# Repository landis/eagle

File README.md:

eagle
=====

eagle schematics and boards

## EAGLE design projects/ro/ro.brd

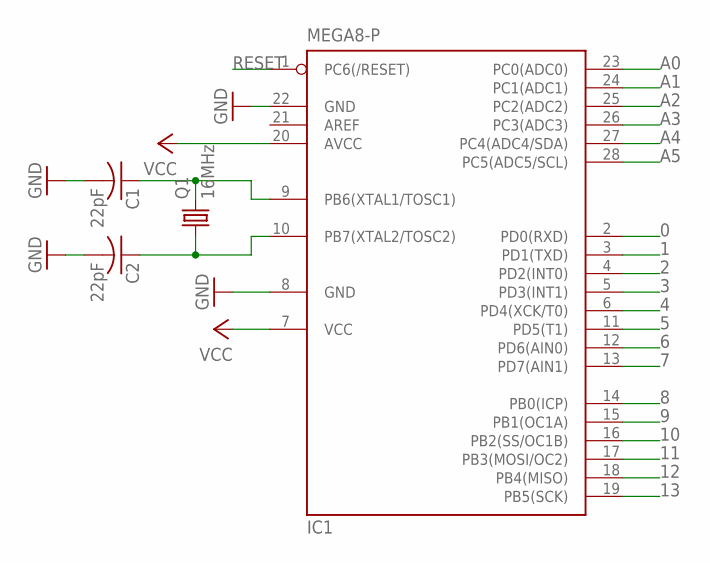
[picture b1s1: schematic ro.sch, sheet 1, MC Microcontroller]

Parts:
C1, C2: 22pF; C025-025X050
IC1: MEGA8-P; DIL28-3
Q1: 16MHz; HC49/S

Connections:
0: IC1.2 (PD0(RXD))
1: IC1.3 (PD1(TXD))
2: IC1.4 (PD2(INT0)); also elsewhere on the board
3: IC1.5 (PD3(INT1)); also elsewhere on the board
4: IC1.6 (PD4(XCK/T0))
5: IC1.11 (PD5(T1))
6: IC1.12 (PD6(AIN0))
7: IC1.13 (PD7(AIN1)); also elsewhere on the board
8: IC1.14 (PB0(ICP)); also elsewhere on the board
9: IC1.15 (PB1(OC1A)); also elsewhere on the board
10: IC1.16 (PB2(SS/OC1B)); also elsewhere on the board
11: IC1.17 (PB3(MOSI/OC2)); also elsewhere on the board
12: IC1.18 (PB4(MISO)); also elsewhere on the board
13: IC1.19 (PB5(SCK))
A0: IC1.23 (PC0(ADC0))
A1: IC1.24 (PC1(ADC1))
A2: IC1.25 (PC2(ADC2))
A3: IC1.26 (PC3(ADC3)); also elsewhere on the board
A4: IC1.27 (PC4(ADC4/SDA)); also elsewhere on the board
A5: IC1.28 (PC5(ADC5/SCL)); also elsewhere on the board
GND: C1.2, C2.2, IC1.8 (GND), IC1.22 (GND); also elsewhere on the board
unnamed: C1.1, IC1.9 (PB6(XTAL1/TOSC1)), Q1.2
unnamed: C2.1, IC1.10 (PB7(XTAL2/TOSC2)), Q1.1
RESET: IC1.1 (PC6(/RESET)); also elsewhere on the board
VCC: IC1.7 (VCC), IC1.20 (AVCC); also elsewhere on the board

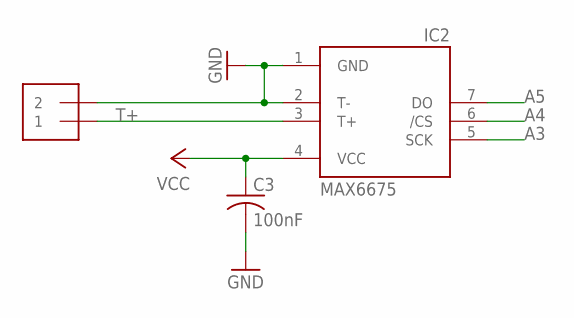
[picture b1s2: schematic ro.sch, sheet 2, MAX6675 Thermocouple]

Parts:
C3: 100nF; C025-025X050
IC2: MAX6675; SO08
TC: 1X2-3.5MM

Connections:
A3: IC2.5 (SCK); also elsewhere on the board
A4: IC2.6 (/CS); also elsewhere on the board
A5: IC2.7 (DO); also elsewhere on the board
GND: C3.2, IC2.1 (GND), IC2.2 (T-), TC.2; also elsewhere on the board
T+: IC2.3 (T+), TC.1
VCC: C3.1, IC2.4 (VCC); also elsewhere on the board

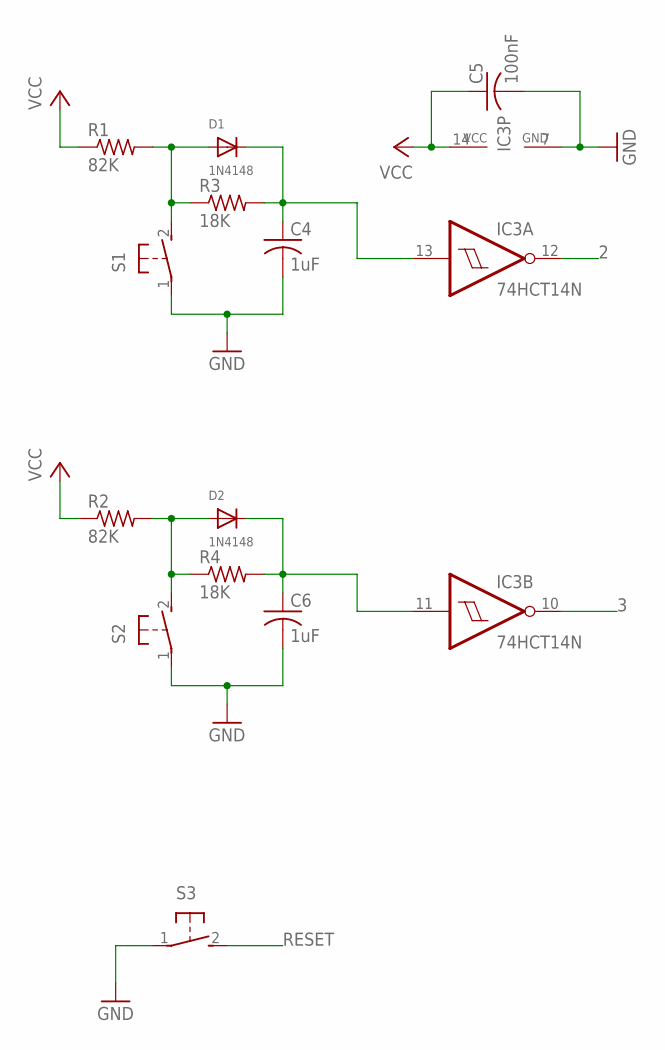
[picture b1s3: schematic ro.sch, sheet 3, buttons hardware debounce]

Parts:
C4, C6: 1uF; C0805
C5: 100nF; C0805
D1, D2: 1N4148; SMADIODE
IC3: 74HCT14N; DIL14
R1, R2: 82K; R0805
R3, R4: 18K; R0805
S1, S2, S3: 31-XX; B3F-31XX

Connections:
2: IC3.12 (O); also elsewhere on the board
3: IC3.10 (O); also elsewhere on the board
GND: C4.2, C5.2, C6.2, IC3.7 (GND), S1.1, S2.1, S3.1; also elsewhere on the board
unnamed: D1.A, R1.2, R3.1, S1.2 (S)
unnamed: D2.A, R2.2, R4.1, S2.2 (S)
unnamed: C4.1, D1.C, IC3.13 (I), R3.2
unnamed: C6.1, D2.C, IC3.11 (I), R4.2
RESET: S3.2 (S); also elsewhere on the board
VCC: C5.1, IC3.14 (VCC), R1.1, R2.1; also elsewhere on the board

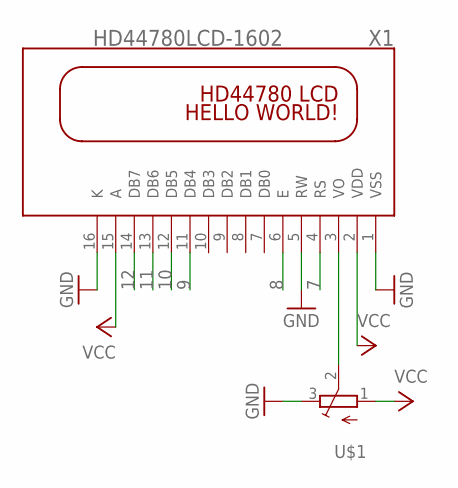
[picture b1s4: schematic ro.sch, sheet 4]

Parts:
U$1: TRIMPOTTC33X; TC33X
X1: HD44780LCD-1602; LCD1602

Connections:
7: X1.4 (RS); also elsewhere on the board
8: X1.6 (E); also elsewhere on the board
9: X1.11 (DB4); also elsewhere on the board
10: X1.12 (DB5); also elsewhere on the board
11: X1.13 (DB6); also elsewhere on the board
12: X1.14 (DB7); also elsewhere on the board
GND: U$1.3 (E), X1.1 (VSS), X1.5 (RW), X1.16 (K); also elsewhere on the board
unnamed: U$1.2 (S), X1.3 (VO)
VCC: U$1.1 (A), X1.2 (VDD), X1.15 (A); also elsewhere on the board

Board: 2 copper layers, 22 parts (1 on the bottom side), 22 nets, no tracks yet.

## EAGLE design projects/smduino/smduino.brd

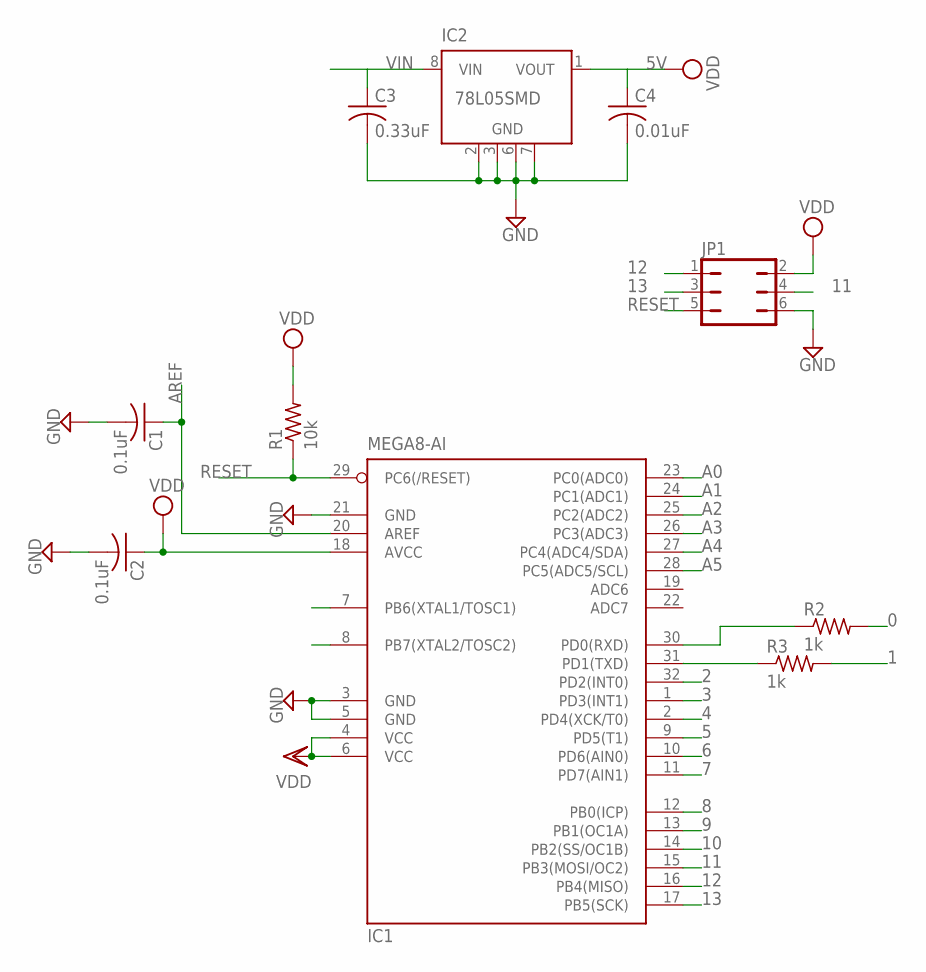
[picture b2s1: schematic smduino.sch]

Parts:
C1, C2: 0.1uF; C0603
C3: 0.33uF; C0603
C4: 0.01uF; C0603
IC1: MEGA8-AI; TQFP32-08
IC2: 78L05SMD; SO08
JP1: JP3Q
R1: 10k; R0603
R2, R3: 1k; R0603

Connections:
0: R2.2
1: R3.2
2: IC1.32 (PD2(INT0))
3: IC1.1 (PD3(INT1))
4: IC1.2 (PD4(XCK/T0))
5: IC1.9 (PD5(T1))
5V: C2.1, C4.1, IC1.4 (VCC), IC1.6 (VCC), IC1.18 (AVCC), IC2.1 (VOUT), JP1.2, R1.2
6: IC1.10 (PD6(AIN0))
7: IC1.11 (PD7(AIN1))
8: IC1.12 (PB0(ICP))
9: IC1.13 (PB1(OC1A))
10: IC1.14 (PB2(SS/OC1B))
11: IC1.15 (PB3(MOSI/OC2)), JP1.4
12: IC1.16 (PB4(MISO)), JP1.1
13: IC1.17 (PB5(SCK)), JP1.3
A0: IC1.23 (PC0(ADC0))
A1: IC1.24 (PC1(ADC1))
A2: IC1.25 (PC2(ADC2))
A3: IC1.26 (PC3(ADC3))
A4: IC1.27 (PC4(ADC4/SDA))
A5: IC1.28 (PC5(ADC5/SCL))
AREF: C1.1, IC1.20 (AREF)
GND: C1.2, C2.2, C3.2, C4.2, IC1.3 (GND), IC1.5 (GND), IC1.21 (GND), IC2.2 (GND), IC2.3 (GND), IC2.6 (GND), IC2.7 (GND), JP1.6
unnamed: IC1.30 (PD0(RXD)), R2.1
unnamed: IC1.31 (PD1(TXD)), R3.1
RESET: IC1.29 (PC6(/RESET)), JP1.5, R1.1
VIN: C3.1, IC2.8 (VIN)
XTAL1: IC1.7 (PB6(XTAL1/TOSC1))
XTAL2: IC1.8 (PB7(XTAL2/TOSC2))

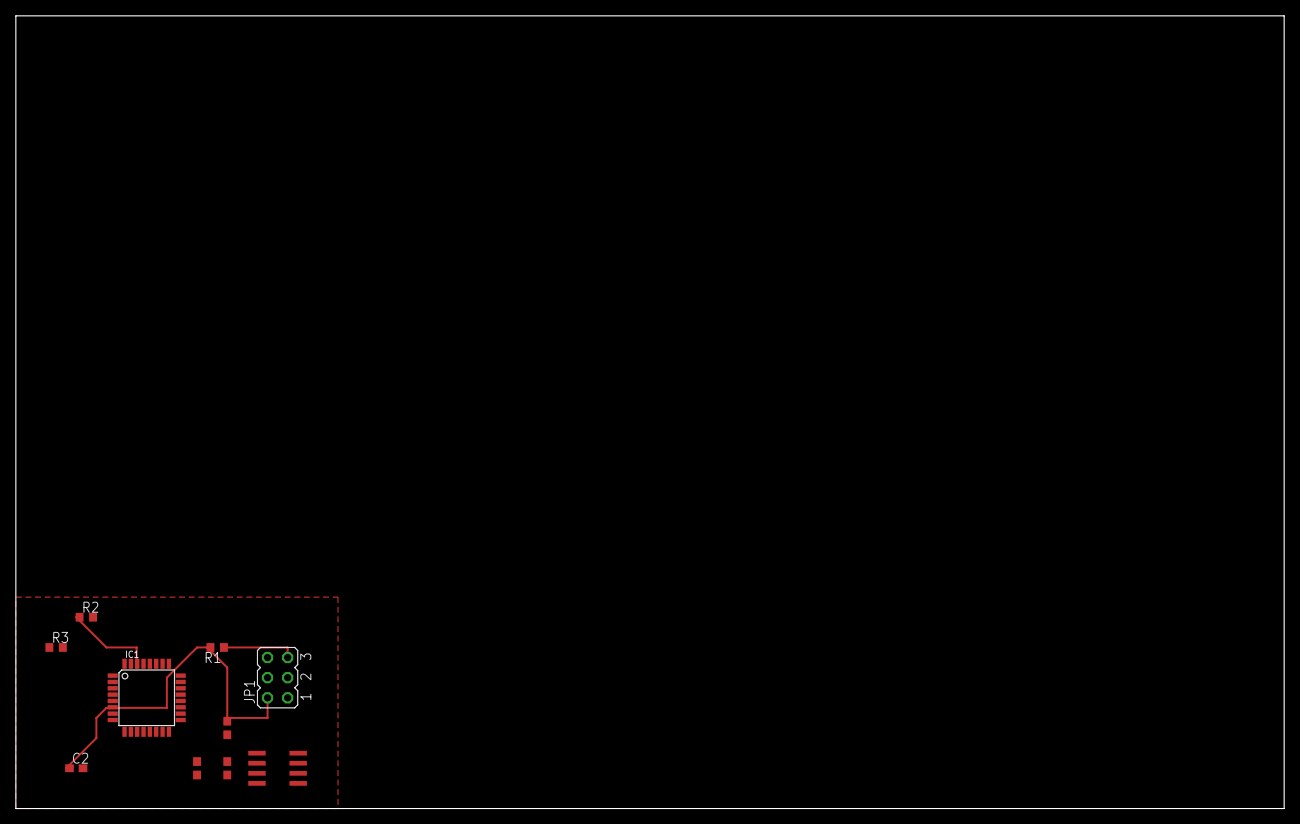
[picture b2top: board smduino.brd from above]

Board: 2 copper layers, 160.0 x 100.0 mm, 10 parts (0 on the bottom side), 10 nets.

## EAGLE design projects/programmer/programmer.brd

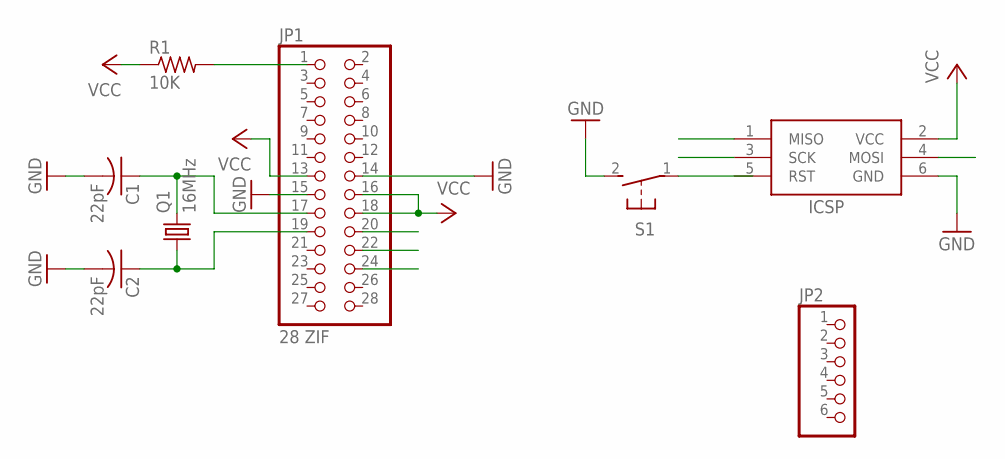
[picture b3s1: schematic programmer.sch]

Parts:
C1, C2: 22pF; C025-025X050
ICSP: AVRISP-6; AVRISP
JP1: 28 ZIF; 2X14
JP2: PINHD-1X6; 1X06
Q1: 16MHz; HC49/S
R1: 10K; 0207/10
S1: 31-XX; B3F-31XX

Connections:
GND: C1.2, C2.2, ICSP.6 (GND), JP1.14, JP1.15, S1.2 (S)
MISO: ICSP.1 (MISO), JP1.22
MOSI: ICSP.4 (MOSI), JP1.24
unnamed: C1.1, JP1.17, Q1.2
unnamed: C2.1, JP1.19, Q1.1
RESET: JP1.1, R1.2, S1.1
SCK: ICSP.3 (SCK), JP1.20
VCC: ICSP.2 (VCC), JP1.13, JP1.16, JP1.18, R1.1

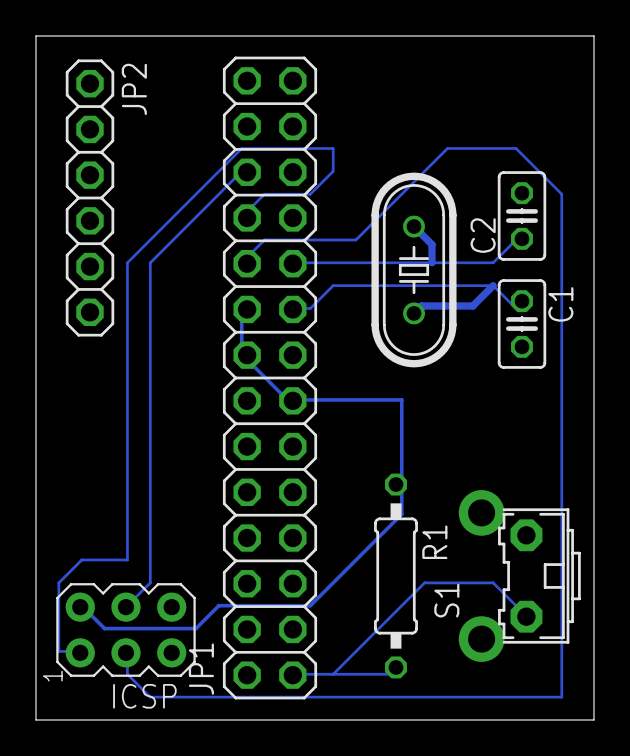
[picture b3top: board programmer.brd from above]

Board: 2 copper layers, 31.0 x 38.0 mm, 8 parts (0 on the bottom side), 8 nets.

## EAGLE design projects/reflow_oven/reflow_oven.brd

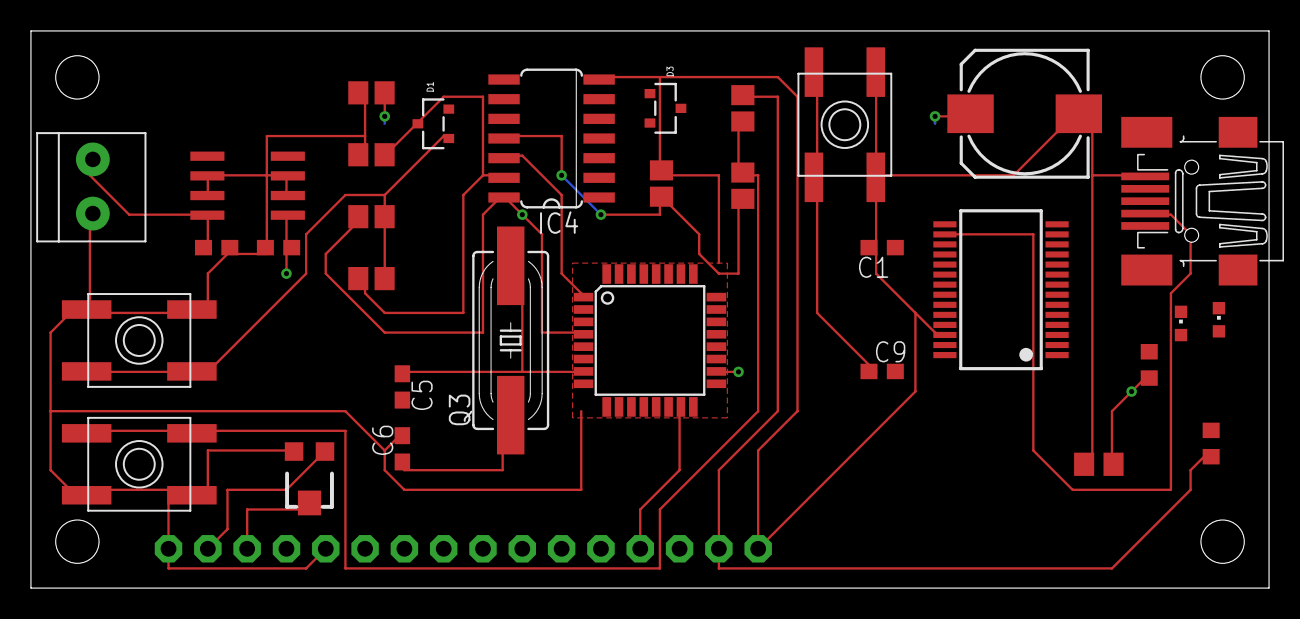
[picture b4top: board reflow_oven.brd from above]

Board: 2 copper layers, 80.0 x 36.0 mm, 34 parts (0 on the bottom side), 29 nets.

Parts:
C1, C5, C6, C9: C0603
C2: 0.1uF; C0805
C3: 10uF; 175TMP-0810
C7: 0.01uF; C0603
C8: 0.33uF; C0603
C10, C11: 1uF; C0805
C12: 100nF; C0805
D1, D3: 1N4148; SOT23-R
IC1: MEGA8-AI; TQFP32-08
IC2: 78L05SMD; SO08
IC3: FT232RL; SSOP28
IC4: 74HC14D; SO14
J1: 1X2-3.5MM
JP1, JP2: 1X08-CLEANBIG
LED1: Red; CHIPLED_0603
LED2: Green; CHIPLED_0603
Q3: 16MHz; SM49
R1, R2: 1k; R0603
R5, R6: 82k; R0805
R7, R8: 18k; R0805
SW1: RST SW; EVQ-Q2
SW2: D3 SW; EVQ-Q2
SW3: D2 SW; EVQ-Q2
U$1: 10k; TC33X
X1: USB; 32005-201

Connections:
0: IC1.30, IC3.1
1: IC1.31, IC3.5
2: IC1.32, IC4.10
3: IC1.1, IC4.12
5V: C2.1, C3.+, C7.1, C12.1, IC1.4, IC1.6, IC1.18, IC2.1, IC3.20, IC4.14, JP1.2, JP2.7, R1.2, R2.2, R5.1, R6.1, U$1.1, X1.1
7: IC1.11, JP1.4
8: IC1.12, JP1.6
9: IC1.13, JP2.3
10: IC1.14, JP2.4
11: IC1.15, JP2.5
12: IC1.16, JP2.6
D+DP: IC3.15, X1.3
D-DM: IC3.16, X1.2
DTR: C9.2, IC3.2
GND: C1.2, C2.2, C3.-, C5.2, C6.2, C7.2, C8.2, C10.2, C11.2, C12.2, IC1.3, IC1.5, IC1.21, IC2.2, IC2.3, IC2.6, IC2.7, IC3.7, IC3.18, IC3.21, IC3.25, IC3.26, IC4.7, J1.1, JP1.1, JP1.5, JP2.8, SW1.B, SW1.B', SW2.A, SW2.A', SW3.A, SW3.A', U$1.3, X1.5
L3: JP1.3, U$1.2
unnamed: LED2.A, R2.1
unnamed: LED1.A, R1.1
unnamed: D1.1, R5.2, R8.1, SW2.B, SW2.B'
unnamed: C11.1, D1.3, IC4.13, R8.2
unnamed: D3.1, R6.2, R7.1, SW3.B, SW3.B'
unnamed: C10.1, D3.3, IC4.11, R7.2
PWRIN: C8.1, IC2.8, J1.2
RESET: C9.1, IC1.29, SW1.A, SW1.A'
RXLED: IC3.22, LED2.C
TXLED: IC3.23, LED1.C
VCCIO: C1.1, IC3.17
XTAL1: C5.1, IC1.7, Q3.2
XTAL2: C6.1, IC1.8, Q3.1

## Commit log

2012-05-12 started reflow_oven
2012-05-12 removing temp files
2012-05-12 add pdf previews
2012-05-13 think the ftdi chip is done. also did a good deal of the arduino setup.
2012-05-13 add DC Jack
2012-05-15 button debounce start
2012-05-15 lcduino
2012-05-15 some board edits
2012-05-15 better layout of board
2012-05-15 changing parts again, now down to 0603 size
2012-05-26 yet another reboot of the reflow
2012-05-26 programmer dummy mockup
2012-05-31 more design
